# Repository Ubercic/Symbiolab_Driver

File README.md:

# Symbiolab Driver

## Overwiev 

Symbiolab driver was developed by institute IRNAS Rače for symbiolab biolaboratory. Its goal is to be used in as much as possible DIY laboratory equipment created for symbiolab's professional use in their research. A full list of planned DIY equipment can be found [here](https://github.com/symbiolab/bio-labware/blob/master/010_general_preparation.md). To achieve the most diverse use for the driver, we decidet to use a modular design, the most common components(display, encoder..) will be included in the driver, where as the design specific components(relay, ESC) are to be on a separate module.

## Table of contents

* Overwiev
* Table of contents
* Design specification
* Power supply config
* Board layout
* Pinout definition
* Testing
* Schemetics
* Featured installments

## Design specification

* [Nodemcu](http://nodemcu.com/index_en.html)
* Incremental encoder
* [I2C OLED display](https://www.adafruit.com/product/326)
* Motor driver [DRV8825](https://www.pololu.com/product/2133)
* Analog in pins for sensor readings
* 12V power supply
* mount screws

## Power supply config

Most of the desired elements controled with the driver work on 12 volts, to bring down the voltage to the required 5V in the Vin pin for the nodemcu we use a TLV1117 voltege regulator. Avidional voltage ripple tantal capacitors are wired before and after the regulator. to switch the nodemcu on and off, we added a power switch on the 12V line before the TLV1117. The nodemcu voltage level is 3V, but it takes 5V input.

## Board layout 

The PCB is designed to be montued as a faceplate on the lab equippment. Therefore most of the components are on the back ob the board. On the front there are the OLED display and incremental encoder, for the user control. All of the nodemcu pins are arranged in a raspberry pinout, this enables the use of raspberry shields.
The only analog pin on the nodemcu is separate with the 3v3 and GND pins next to it.

## Pinout definiton

## Testing

## Schematics

The schematic and PCB design were crated with the free CAD software KiCAD.

## Featured installments

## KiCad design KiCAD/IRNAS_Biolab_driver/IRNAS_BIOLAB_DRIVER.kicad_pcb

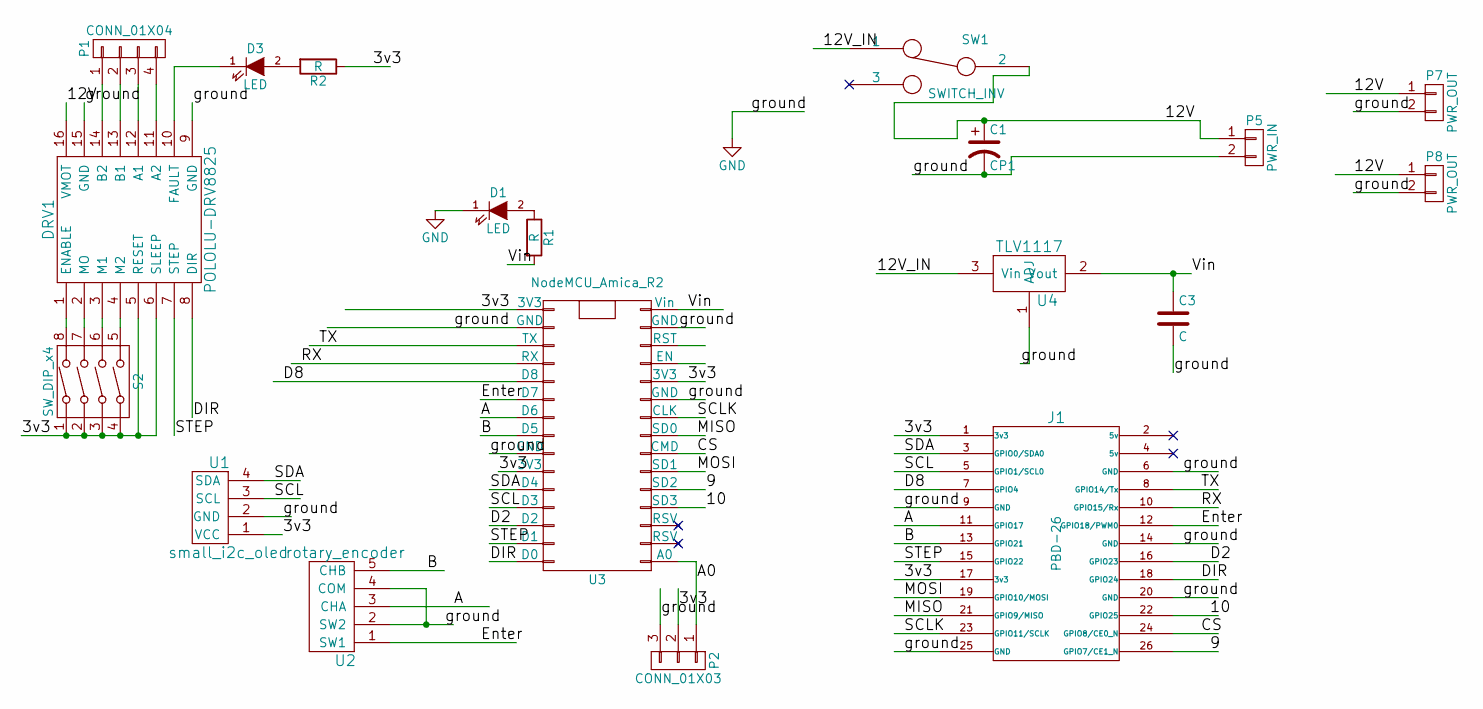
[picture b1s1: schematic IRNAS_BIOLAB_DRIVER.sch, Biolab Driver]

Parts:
C1: CP1; TantalC_SizeB_EIA-3528_HandSoldering
C3: C; TantalC_SizeB_EIA-3528_HandSoldering
D1, D3: LED; LED_0603
DRV1: POLOLU-DRV8825
J1: PBD-26; Socket_Strip_Straight_2x13
P1: CONN_01X04; Pin_Header_Straight_1x04
P2: CONN_01X03; Pin_Header_Straight_1x03
P5: PWR_IN; Power_universal
P7, P8: PWR_OUT; Terminal_block_5mm
R1, R2: R; R_0603_HandSoldering
S2: SW_DIP_x4; SW_DIP_x4_Slide
SW1: SWITCH_INV; OS102011MA1QN1_slide_switch
U1: small_i2c_oled; Small_I2C_OLED
U2: rotary_encoder; rotary_enc_bourns_EC12R-4215F-S0024
U3: NodeMCU_Amica_R2
U4: TLV1117

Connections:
/3v3: DRV1.5 (RESET), DRV1.6 (SLEEP), J1.1 (3v3), J1.17 (3v3), P2.2, R2.1, S2.1, S2.2, S2.3, S2.4, U1.1 (VCC), U3.11 (3V3), U3.16 (3V3), U3.25 (3V3)
/9: J1.26 (GPIO7/CE1_N), U3.5 (SD2)
/10: J1.22 (GPIO25), U3.4 (SD3)
/12V: C1.1, DRV1.16 (VMOT), P5.1, P7.1, P8.1, SW1.2
/12V_IN: SW1.1, U4.3 (Vin)
/A: J1.11 (GPIO17), U2.3 (CHA), U3.22 (D6)
/A0: P2.1, U3.1 (A0)
/B: J1.13 (GPIO21), U2.5 (CHB), U3.23 (D5)
/CS: J1.24 (GPIO8/CE0_N), U3.7 (CMD)
/D2: J1.16 (GPIO23), U3.28 (D2)
/D8: J1.7 (GPIO4), U3.20 (D8)
/DIR: DRV1.8 (DIR), J1.18 (GPIO24), U3.30 (D0)
/Enter: J1.12 (GPIO18/PWM0), U2.1 (SW1), U3.21 (D7)
/MISO: J1.21 (GPIO9/MISO), U3.8 (SD0)
/MOSI: J1.19 (GPIO10/MOSI), U3.6 (SD1)
/RX: J1.10 (GPIO15/Rx), U3.19 (RX)
/SCL: J1.5 (GPIO1/SCL0), U1.3 (SCL), U3.27 (D3)
/SCLK: J1.23 (GPIO11/SCLK), U3.9 (CLK)
/SDA: J1.3 (GPIO0/SDA0), U1.4 (SDA), U3.26 (D4)
/STEP: DRV1.7 (STEP), J1.15 (GPIO22), U3.29 (D1)
/TX: J1.8 (GPIO14/Tx), U3.18 (TX)
/Vin: C3.1, R1.2, U3.15 (Vin), U4.2 (Vout)
GND: C1.2, C3.2, D1.1 (K), DRV1.9 (GND), DRV1.15 (GND), J1.6 (GND), J1.9 (GND), J1.14 (GND), J1.20 (GND), J1.25 (GND), P2.3, P5.2, P7.2, P8.2, U1.2 (GND), U2.2 (SW2), U2.4 (COM), U3.10 (GND), U3.14 (GND), U3.17 (GND), U3.24 (GND), U4.1 (ADJ)
unnamed: D1.2 (A), R1.1
unnamed: D3.1 (K), DRV1.10 (FAULT)
unnamed: D3.2 (A), R2.2
unnamed: DRV1.1 (ENABLE), S2.8
unnamed: DRV1.2 (MO), S2.7
unnamed: DRV1.3 (M1), S2.6
unnamed: DRV1.4 (M2), S2.5
unnamed: DRV1.11 (A2), P1.4
unnamed: DRV1.12 (A1), P1.3
unnamed: DRV1.13 (B1), P1.2
unnamed: DRV1.14 (B2), P1.1

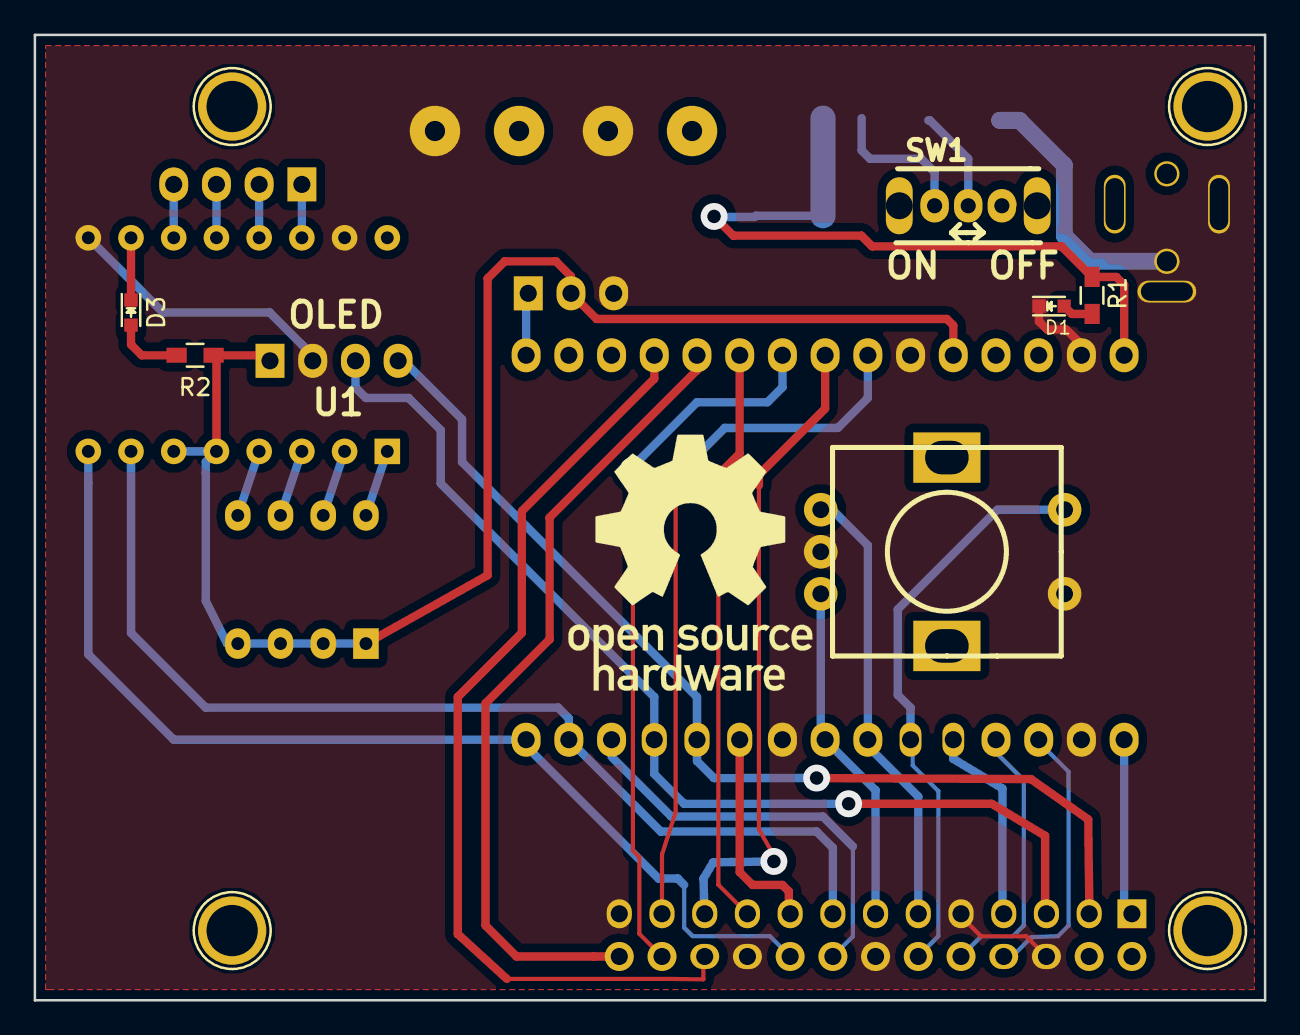
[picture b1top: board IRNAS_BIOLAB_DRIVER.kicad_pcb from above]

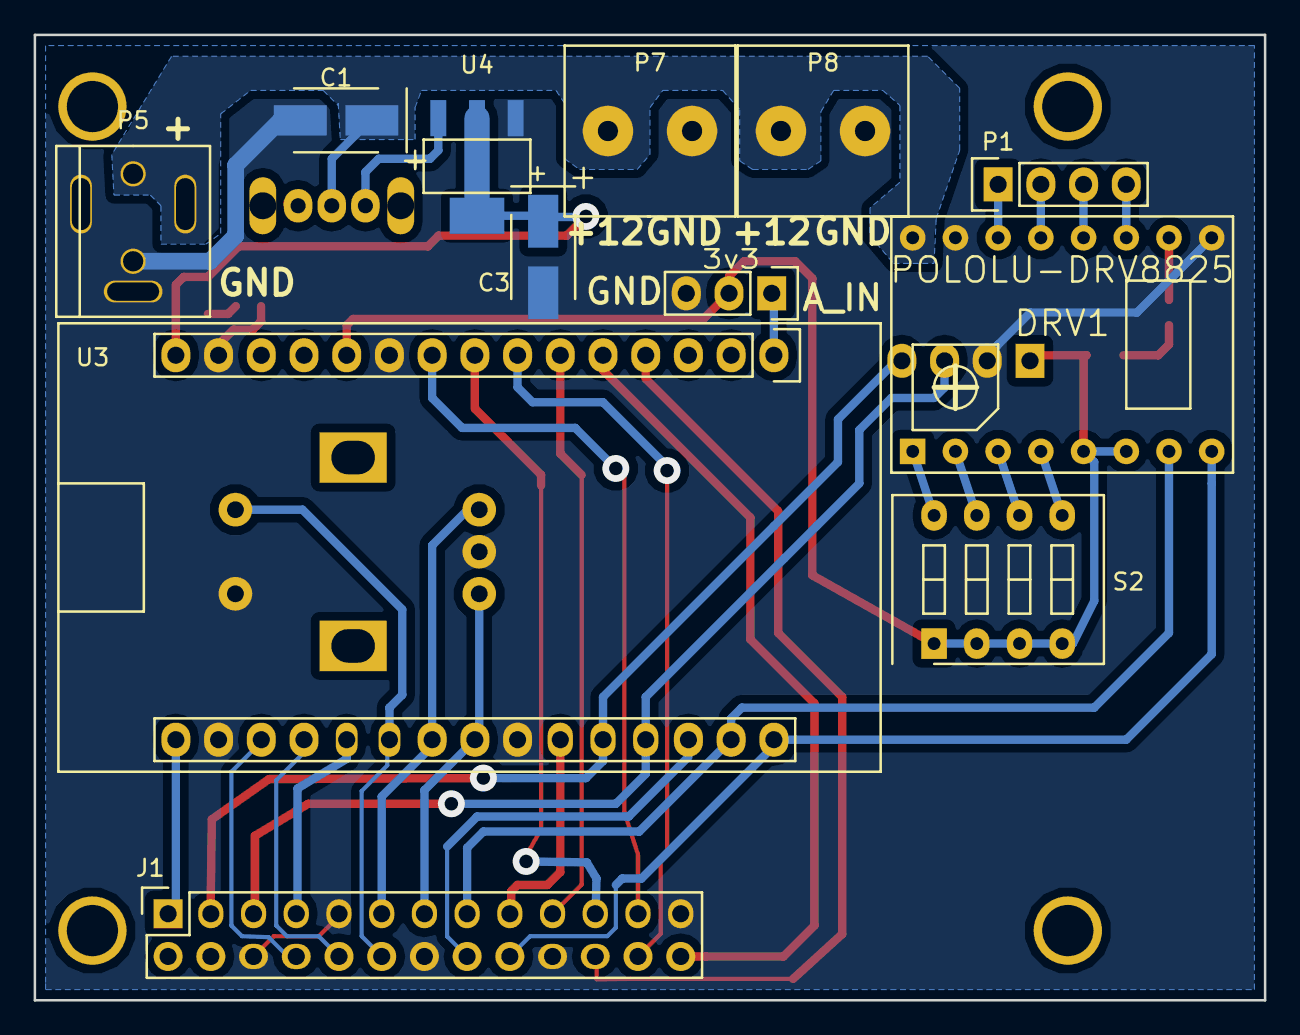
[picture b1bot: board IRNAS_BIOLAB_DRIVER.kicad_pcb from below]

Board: 2 copper layers, 73.2 x 57.4 mm, 19 parts (12 on the bottom side), 34 nets.

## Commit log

2017-04-11 :circus_tent: Added .gitattributes & .gitignore files
2017-04-11 added first files
2017-04-28 pre publishing
2017-04-28 renamed readme
2017-04-29 updated readme and added pinout png
    removed xls too
